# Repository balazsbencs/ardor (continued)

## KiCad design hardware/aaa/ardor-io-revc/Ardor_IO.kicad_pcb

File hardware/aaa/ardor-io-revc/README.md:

# Ardor IO — Rev C, budget SMT

Rev C is an alternate 68 × 46 mm, two-layer board for two-board JLCPCB SMT assembly. It retains DIN MIDI input, passive expression input, mono line output with startup relay mute, and the internal amp feed. Headphones are omitted. The full-featured revision remains in [../ardor-io](../ardor-io/README.md).

Open `Ardor_IO.kicad_pro` in KiCad 9. Use the [connected one-page schematic](review/Ardor_IO_connected.pdf) to follow the circuit, or [Ardor_IO.pdf](Ardor_IO.pdf) for the five editable schematic sheets. The [assembly guide](assembly/README.md) contains the Gerber ZIP, exact JLCPCB BOM, CPL and placement reference.

| For two assembled boards | Previous revision | Rev C |
| --- | ---: | ---: |
| SMT placements per board | 76 | 60 |
| Unique SMT parts | 28 | 24 |
| Extended part types | 15 | 8 |
| Modelled components, including minimums/loss | $39.06 | $16.57 |
| Economic feeder fees at $3.07/type | $46.05 | $24.56 |
| Components + feeder subtotal | $85.11 | $41.13 |

This model predicts **$43.98 less for two boards** in components and feeder fees. It is not a checkout quotation or a guaranteed total. PCB fabrication, setup, stencil, joints, shipping, tax, fixtures, manual parts and discounts are outside the subtotal. The earlier user quote was $108 for two assembled boards; its fee breakdown was not provided. See [cost-comparison.json](assembly/cost-comparison.json), the dated inventory snapshots and [JLCPCB's current price schedule](https://jlcpcb.com/help/article/pcb-assembly-price). Rev C also removes the headphone QFN and its X-ray inspection requirement.

## Changes and tradeoffs

- Two TI TLV9002IDR SOIC-8 dual op-amps replace three OPA2320 devices. The mono buffer feeds two separate coupling capacitors and source resistors. The line and amp outputs share this buffer; simultaneous loads must meet the specified minimum impedances.
- ADS1115, address 0x48, GPIO mapping, pedal polarity selector, H11L1M optocoupler, relay driver and jack protection remain. Firmware can keep the existing MIDI, expression and line-mute interfaces. GPIO17 is unused.
- Mono averaging resistors are 10 kΩ / 1%, shared with other Basic resistors. Worst-case weights are 0.495 and 0.505; opposite-phase inputs can leave a 1% residual, instead of the previous 0.1% resistor target.
- Supply bulk and audio coupling capacitors use Basic Samsung X5R parts. The 50 V, 1206 audio capacitors retain their nominal 10 µF. X5R has a lower temperature limit than X7R and still has voltage-dependent capacitance, microphonics and distortion that require measurement.
- The three 0603 ferrites are Basic Murata BLM18PG121SN1D, 120 Ω at 100 MHz rather than 600 Ω. DC operation is retained; RF attenuation changes. No assembled-enclosure EMC claim is made.
- The outline and mounting coordinates match the compact board. Removed circuitry leaves spare area; enclosure fit, Pi stack height and panel-jack choices still need mechanical confirmation.
- Ground uses the filled front/back copper: 192 redundant GND track segments (324.13 mm) are removed. Three short local links and all 20 ground vias remain. See the [before/after routing view](routing/ground-routing.svg) and [ground audit](verification/ground-routing-audit.json). CHASSIS and signal routing are unchanged. A smaller outline would require moving components and mounting holes; removing tracks alone does not create that mechanical clearance.
- Both 3.3 V rails use uniform 0.20 mm tracks. Their low current makes wider runs unnecessary; the [width audit](verification/3v3-width-audit.json) checks every segment and a conservative track-resistance estimate. All other track widths and all route centerlines retain the reviewed layout.

The board passes all-severity ERC and DRC, with zero unconnected or parity findings and no exclusions. [Connectivity audit](verification/connectivity-audit.json) checks all **219 electrical pad/net assignments** and 199 intended non-NC connections. The one-page drawing separately checks coverage of all 80 components and wire geometry. This is an engineering prototype; audio, hot-plug, startup and enclosure tests have not been performed.

Read [DESIGN_NOTES.md](DESIGN_NOTES.md) before building. SMT is assembled by JLCPCB; headers, optocoupler, relay, panel connectors and shunts are fitted by hand.

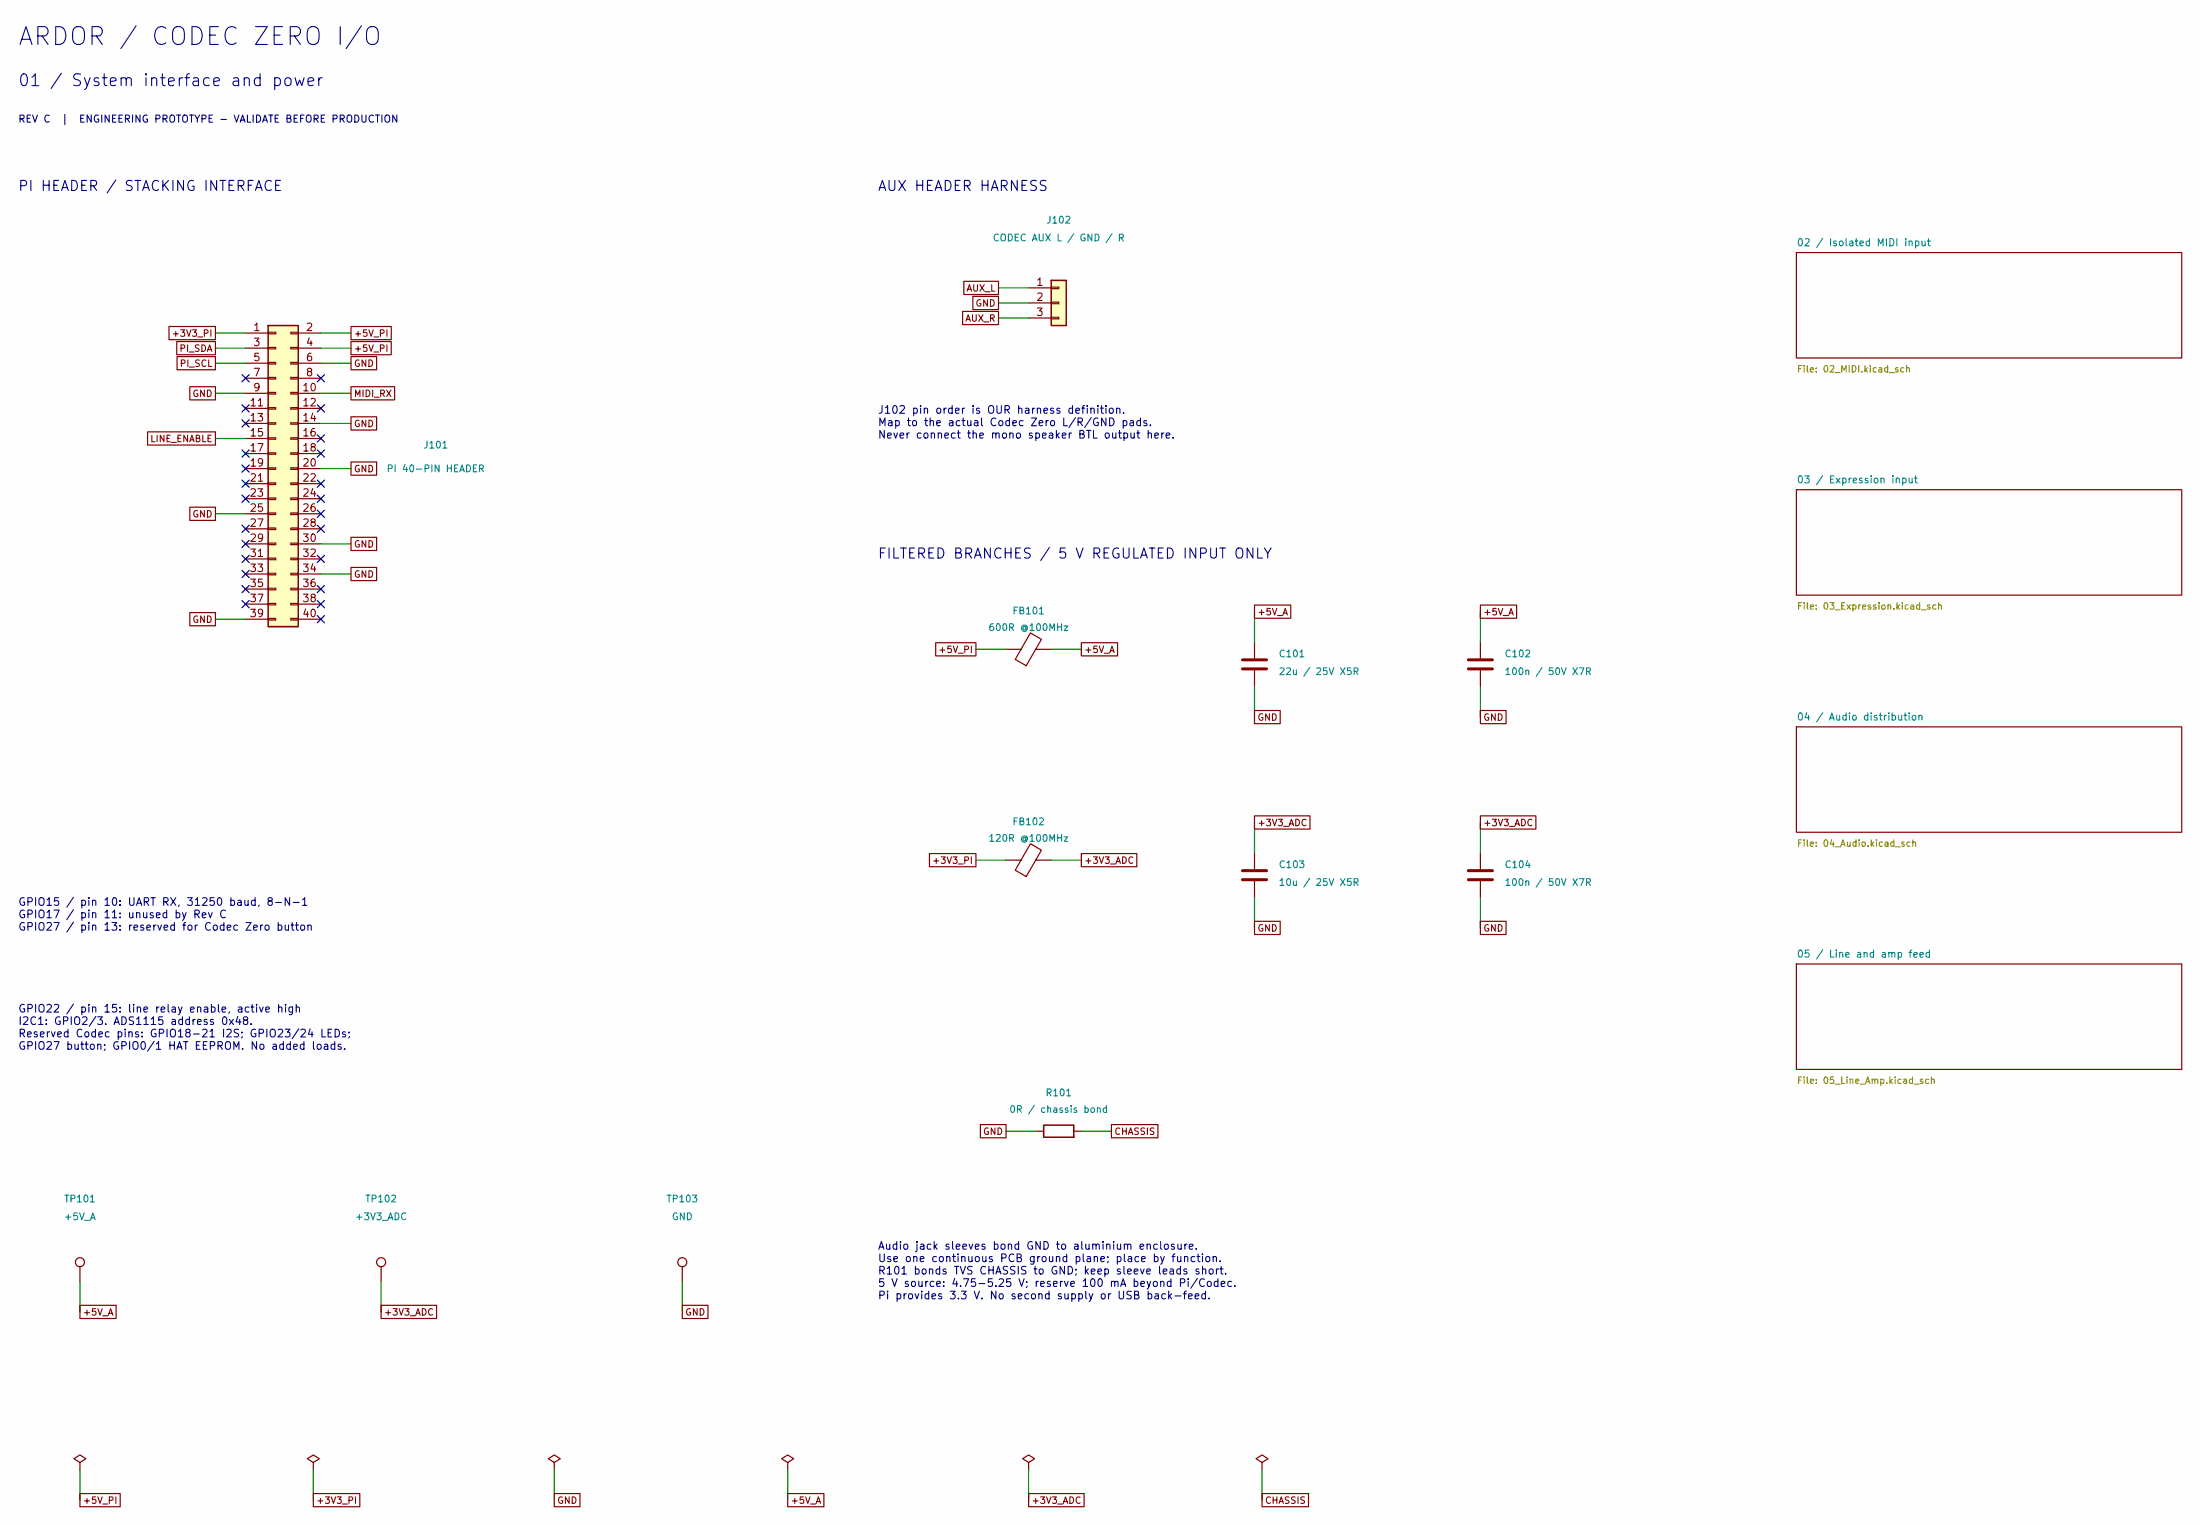
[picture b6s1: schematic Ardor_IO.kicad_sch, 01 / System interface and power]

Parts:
C101: 22u / 25V X5R; C_0805_2012Metric; MPN Samsung Electro-Mechanics CL21A226MAQNN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; JLCPCB Part # C45783
C102, C104: 100n / 50V X7R; C_0603_1608Metric; MPN YAGEO CC0603KRX7R9BB104; JLCPCB Part # C14663
C103: 10u / 25V X5R; C_0805_2012Metric; MPN Samsung Electro-Mechanics CL21A106KAYNN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; JLCPCB Part # C15850
FB101: 600R @100MHz; L_0805_2012Metric; MPN Murata BLM21PG601SN1D; JLCPCB Part # C41556732
FB102: 120R @100MHz; R_0603_1608Metric; MPN Murata Electronics BLM18PG121SN1D; JLCPCB Part # C14709
J101: PI 40-PIN HEADER; PinSocket_2x20_P2.54mm_Vertical; MPN Samtec SSQ-120-03-G-D (verify stack hei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
J102: CODEC AUX L / GND / R; PinHeader_1x03_P2.54mm_Vertical
R101: 0R / chassis bond; R_1206_3216Metric; MPN UNI-ROYAL 1206W4F0000T5E; JLCPCB Part # C17888
TP101: +5V_A; TestPoint_Pad_D1.5mm
TP102: +3V3_ADC; TestPoint_Pad_D1.5mm
TP103: GND; TestPoint_Pad_D1.5mm

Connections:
+3V3_ADC: C103.1, C104.1, FB102.2, TP102.1; also elsewhere on the board
+3V3_PI: FB102.1, J101.1; also elsewhere on the board
+5V_A: C101.1, C102.1, FB101.2, TP101.1; also elsewhere on the board
+5V_PI: FB101.1, J101.2, J101.4; also elsewhere on the board
AUX_L: J102.1; also elsewhere on the board
AUX_R: J102.3; also elsewhere on the board
CHASSIS: R101.2; also elsewhere on the board
GND: C101.2, C102.2, C103.2, C104.2, J101.6, J101.9, J101.14, J101.20, J101.25, J101.30, J101.34, J101.39, J102.2, R101.1, TP103.1; also elsewhere on the board
LINE_ENABLE: J101.15; also elsewhere on the board
MIDI_RX: J101.10; also elsewhere on the board
PI_SCL: J101.5; also elsewhere on the board
PI_SDA: J101.3; also elsewhere on the board

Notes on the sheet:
ARDOR / CODEC ZERO I/O
01 / System interface and power
REV C | ENGINEERING PROTOTYPE - VALIDATE BEFORE PRODUCTION
PI HEADER / STACKING INTERFACE
GPIO15 / pin 10: UART RX, 31250 baud, 8-N-1 GPIO17 / pin 11: unused by Rev C GPIO27 / pin 13: reserved for Codec Zero button
GPIO22 / pin 15: line relay enable, active high I2C1: GPIO2/3. ADS1115 address 0x48. Reserved Codec pins: GPIO18-21 I2S; GPIO23/24 LEDs; GPIO27 button; GPIO0/1 HAT EEPROM. No added loads.
AUX HEADER HARNESS
J102 pin order is OUR harness definition. Map to the actual Codec Zero L/R/GND pads. Never connect the mono speaker BTL output here.
FILTERED BRANCHES / 5 V REGULATED INPUT ONLY
Audio jack sleeves bond GND to aluminium enclosure. Use one continuous PCB ground plane; place by function. R101 bonds TVS CHASSIS to GND; keep sleeve leads short. 5 V source: 4.75-5.25 V; reserve 100 mA beyond Pi/Codec. Pi provides 3.3 V. No second supply or USB back-feed.

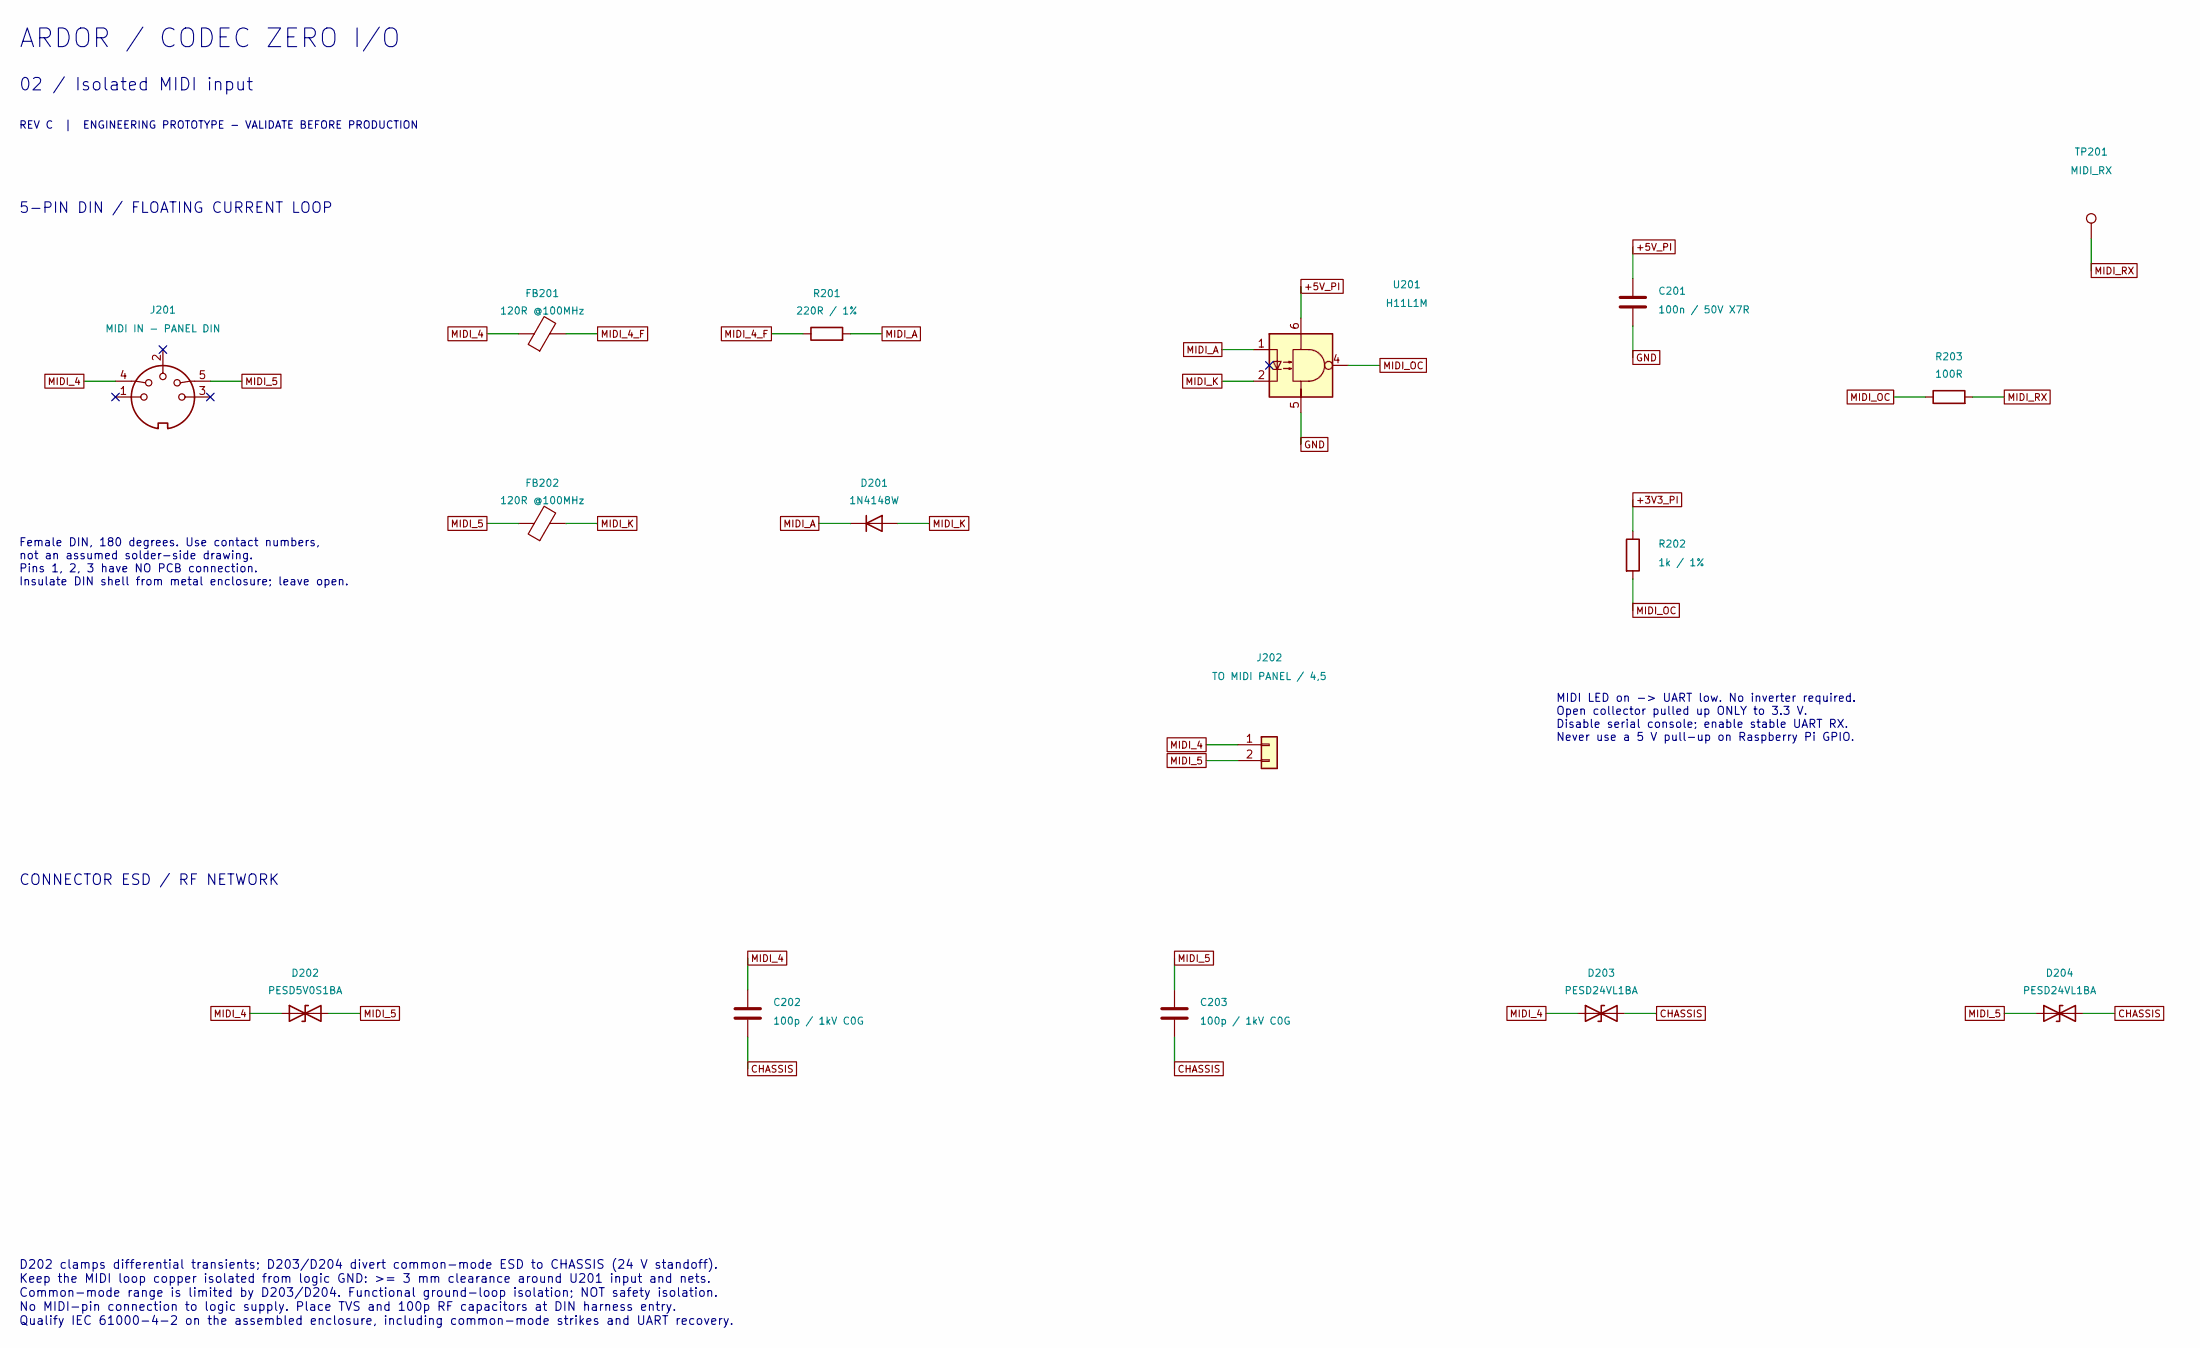
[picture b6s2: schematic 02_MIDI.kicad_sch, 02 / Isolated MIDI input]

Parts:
C201: 100n / 50V X7R; C_0603_1608Metric; MPN YAGEO CC0603KRX7R9BB104; JLCPCB Part # C14663
C202, C203: 100p / 1kV C0G; C_1206_3216Metric; MPN CCTC TCC1206COG101J102DT; JLCPCB Part # C367316
D201: 1N4148W; D_SOD-123; MPN ST(Semtech) 1N4148W; JLCPCB Part # C81598
D202: PESD5V0S1BA; D_SOD-323; MPN Nexperia PESD5V0S1BA,115; JLCPCB Part # C19224
D203, D204: PESD24VL1BA; D_SOD-323; MPN Nexperia PESD24VL1BA,115; JLCPCB Part # C69324
FB201, FB202: 120R @100MHz; R_0603_1608Metric; MPN Murata Electronics BLM18PG121SN1D; JLCPCB Part # C14709
J201: MIDI IN - PANEL DIN
J202: TO MIDI PANEL / 4,5; PinHeader_1x02_P2.54mm_Vertical
R201: 220R / 1%; R_0603_1608Metric; MPN UNI-ROYAL 0603WAF2200T5E; JLCPCB Part # C22962
R202: 1k / 1%; R_0603_1608Metric; MPN UNI-ROYAL 0603WAF1001T5E; JLCPCB Part # C21190
R203: 100R; R_0603_1608Metric; MPN UNI-ROYAL 0603WAF1000T5E; JLCPCB Part # C22775
TP201: MIDI_RX; TestPoint_Pad_D1.5mm
U201: H11L1M; DIP-6_W7.62mm; MPN onsemi H11L1M

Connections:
+3V3_PI: R202.1; also elsewhere on the board
+5V_PI: C201.1, U201.6; also elsewhere on the board
CHASSIS: C202.2, C203.2, D203.2 (A2), D204.2 (A2); also elsewhere on the board
GND: C201.2, U201.5; also elsewhere on the board
MIDI_4: C202.1, D202.1 (A1), D203.1 (A1), FB201.1, J201.4, J202.1
MIDI_4_F: FB201.2, R201.1
MIDI_5: C203.1, D202.2 (A2), D204.1 (A1), FB202.1, J201.5, J202.2
MIDI_A: D201.1 (K), R201.2, U201.1
MIDI_K: D201.2 (A), FB202.2, U201.2
MIDI_OC: R202.2, R203.1, U201.4
MIDI_RX: R203.2, TP201.1; also elsewhere on the board

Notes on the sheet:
ARDOR / CODEC ZERO I/O
02 / Isolated MIDI input
REV C | ENGINEERING PROTOTYPE - VALIDATE BEFORE PRODUCTION
5-PIN DIN / FLOATING CURRENT LOOP
Female DIN, 180 degrees. Use contact numbers, not an assumed solder-side drawing. Pins 1, 2, 3 have NO PCB connection. Insulate DIN shell from metal enclosure; leave open.
MIDI LED on -> UART low. No inverter required. Open collector pulled up ONLY to 3.3 V. Disable serial console; enable stable UART RX. Never use a 5 V pull-up on Raspberry Pi GPIO.
CONNECTOR ESD / RF NETWORK
D202 clamps differential transients; D203/D204 divert common-mode ESD to CHASSIS (24 V standoff). Keep the MIDI loop copper isolated from logic GND: >= 3 mm clearance around U201 input and nets. Common-mode range is limited by D203/D204. Functional ground-loop isolation; NOT safety isolation. No MI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

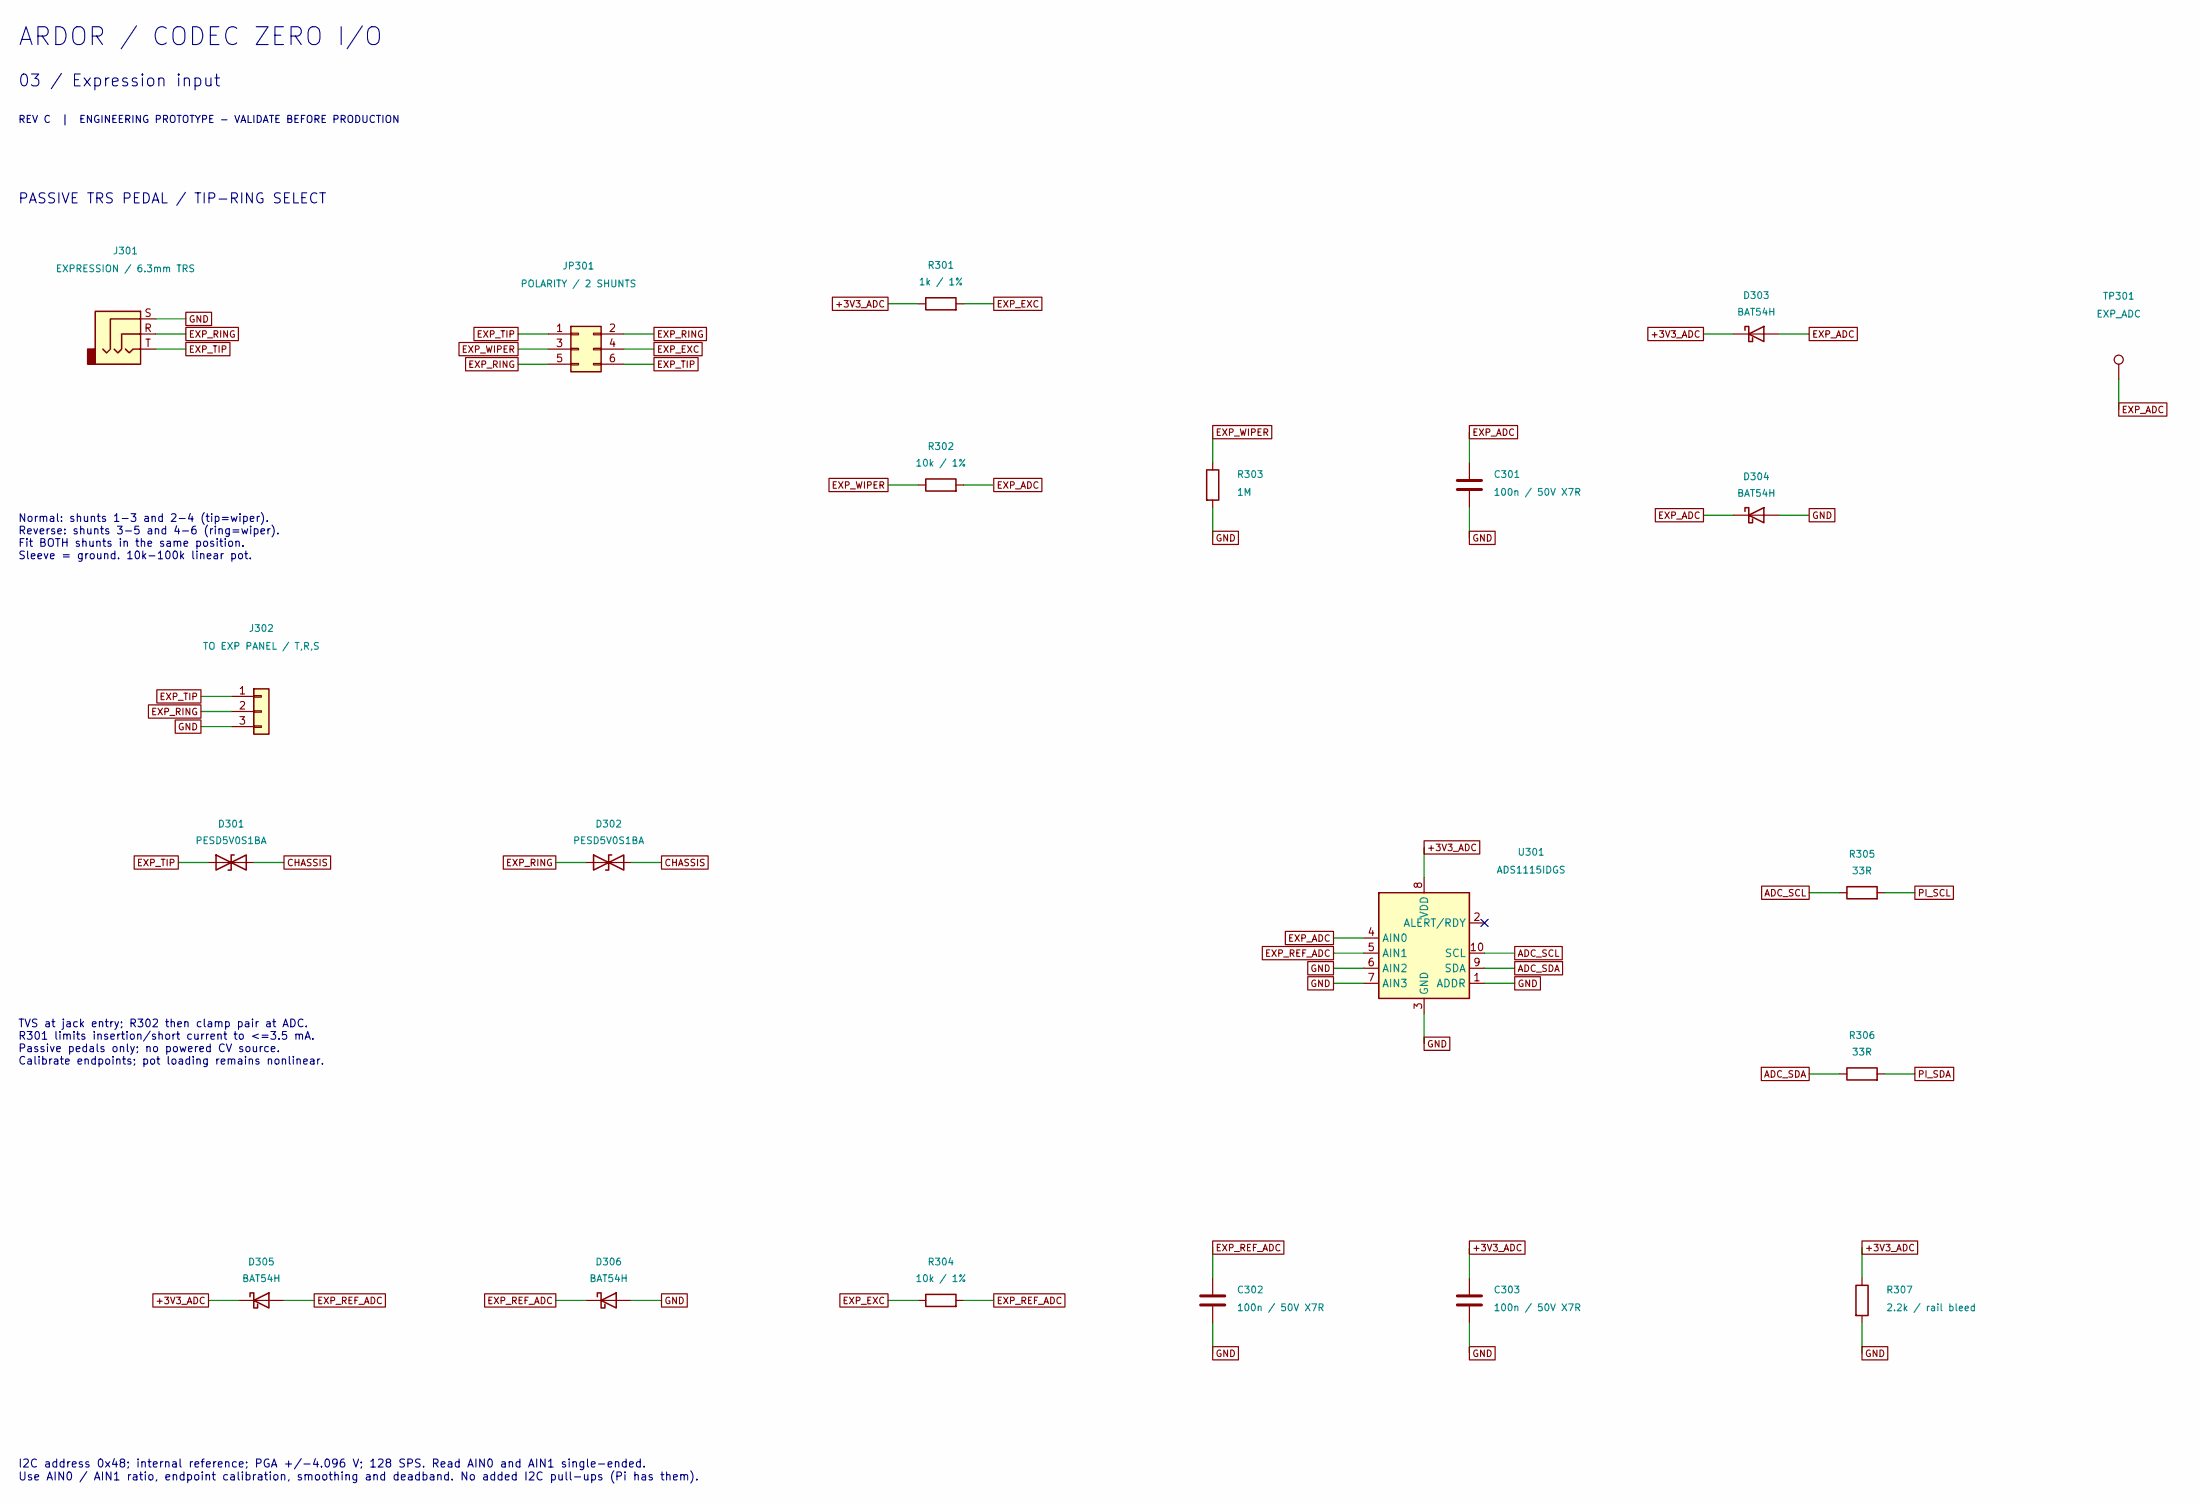
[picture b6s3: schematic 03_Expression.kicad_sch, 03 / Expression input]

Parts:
C301, C302, C303: 100n / 50V X7R; C_0603_1608Metric; MPN YAGEO CC0603KRX7R9BB104; JLCPCB Part # C14663
D301, D302: PESD5V0S1BA; D_SOD-323; MPN Nexperia PESD5V0S1BA,115; JLCPCB Part # C19224
D303, D304, D305, D306: BAT54H; D_SOD-123F; MPN Nexperia BAT54H,115; JLCPCB Part # C426769
J301: EXPRESSION / 6.3mm TRS
J302: TO EXP PANEL / T,R,S; PinHeader_1x03_P2.54mm_Vertical
JP301: POLARITY / 2 SHUNTS; PinHeader_2x03_P2.54mm_Vertical
R301: 1k / 1%; R_0603_1608Metric; MPN UNI-ROYAL 0603WAF1001T5E; JLCPCB Part # C21190
R302, R304: 10k / 1%; R_0603_1608Metric; MPN UNI-ROYAL 0603WAF1002T5E; JLCPCB Part # C25804
R303: 1M; R_0603_1608Metric; MPN UNI-ROYAL 0603WAF1004T5E; JLCPCB Part # C22935
R305, R306: 33R; R_0603_1608Metric; MPN UNI-ROYAL 0603WAF330JT5E; JLCPCB Part # C23140
R307: 2.2k / rail bleed; R_0603_1608Metric; MPN UNI-ROYAL 0603WAF2201T5E; JLCPCB Part # C4190
TP301: EXP_ADC; TestPoint_Pad_D1.5mm
U301: ADS1115IDGS; VSSOP-10_3x3mm_P0.5mm; MPN TI ADS1115IDGSR; JLCPCB Part # C37593

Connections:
+3V3_ADC: C303.1, D303.1 (K), D305.1 (K), R301.1, R307.1, U301.8 (VDD); also elsewhere on the board
ADC_SCL: R305.1, U301.10 (SCL)
ADC_SDA: R306.1, U301.9 (SDA)
CHASSIS: D301.2 (A2), D302.2 (A2); also elsewhere on the board
EXP_ADC: C301.1, D303.2 (A), D304.1 (K), R302.2, TP301.1, U301.4 (AIN0)
EXP_EXC: JP301.4, R301.2, R304.1
EXP_REF_ADC: C302.1, D305.2 (A), D306.1 (K), R304.2, U301.5 (AIN1)
EXP_RING: D302.1 (A1), J301.R, J302.2, JP301.2, JP301.5
EXP_TIP: D301.1 (A1), J301.T, J302.1, JP301.1, JP301.6
EXP_WIPER: JP301.3, R302.1, R303.1
GND: C301.2, C302.2, C303.2, D304.2 (A), D306.2 (A), J301.S, J302.3, R303.2, R307.2, U301.1 (ADDR), U301.3 (GND), U301.6 (AIN2), U301.7 (AIN3); also elsewhere on the board
PI_SCL: R305.2; also elsewhere on the board
PI_SDA: R306.2; also elsewhere on the board

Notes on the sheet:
ARDOR / CODEC ZERO I/O
03 / Expression input
REV C | ENGINEERING PROTOTYPE - VALIDATE BEFORE PRODUCTION
PASSIVE TRS PEDAL / TIP-RING SELECT
Normal: shunts 1-3 and 2-4 (tip=wiper). Reverse: shunts 3-5 and 4-6 (ring=wiper). Fit BOTH shunts in the same position. Sleeve = ground. 10k-100k linear pot.
TVS at jack entry; R302 then clamp pair at ADC. R301 limits insertion/short current to <=3.5 mA. Passive pedals only; no powered CV source. Calibrate endpoints; pot loading remains nonlinear.
I2C address 0x48; internal reference; PGA +/-4.096 V; 128 SPS. Read AIN0 and AIN1 single-ended. Use AIN0 / AIN1 ratio, endpoint calibration, smoothing and deadband. No added I2C pull-ups (Pi has them).

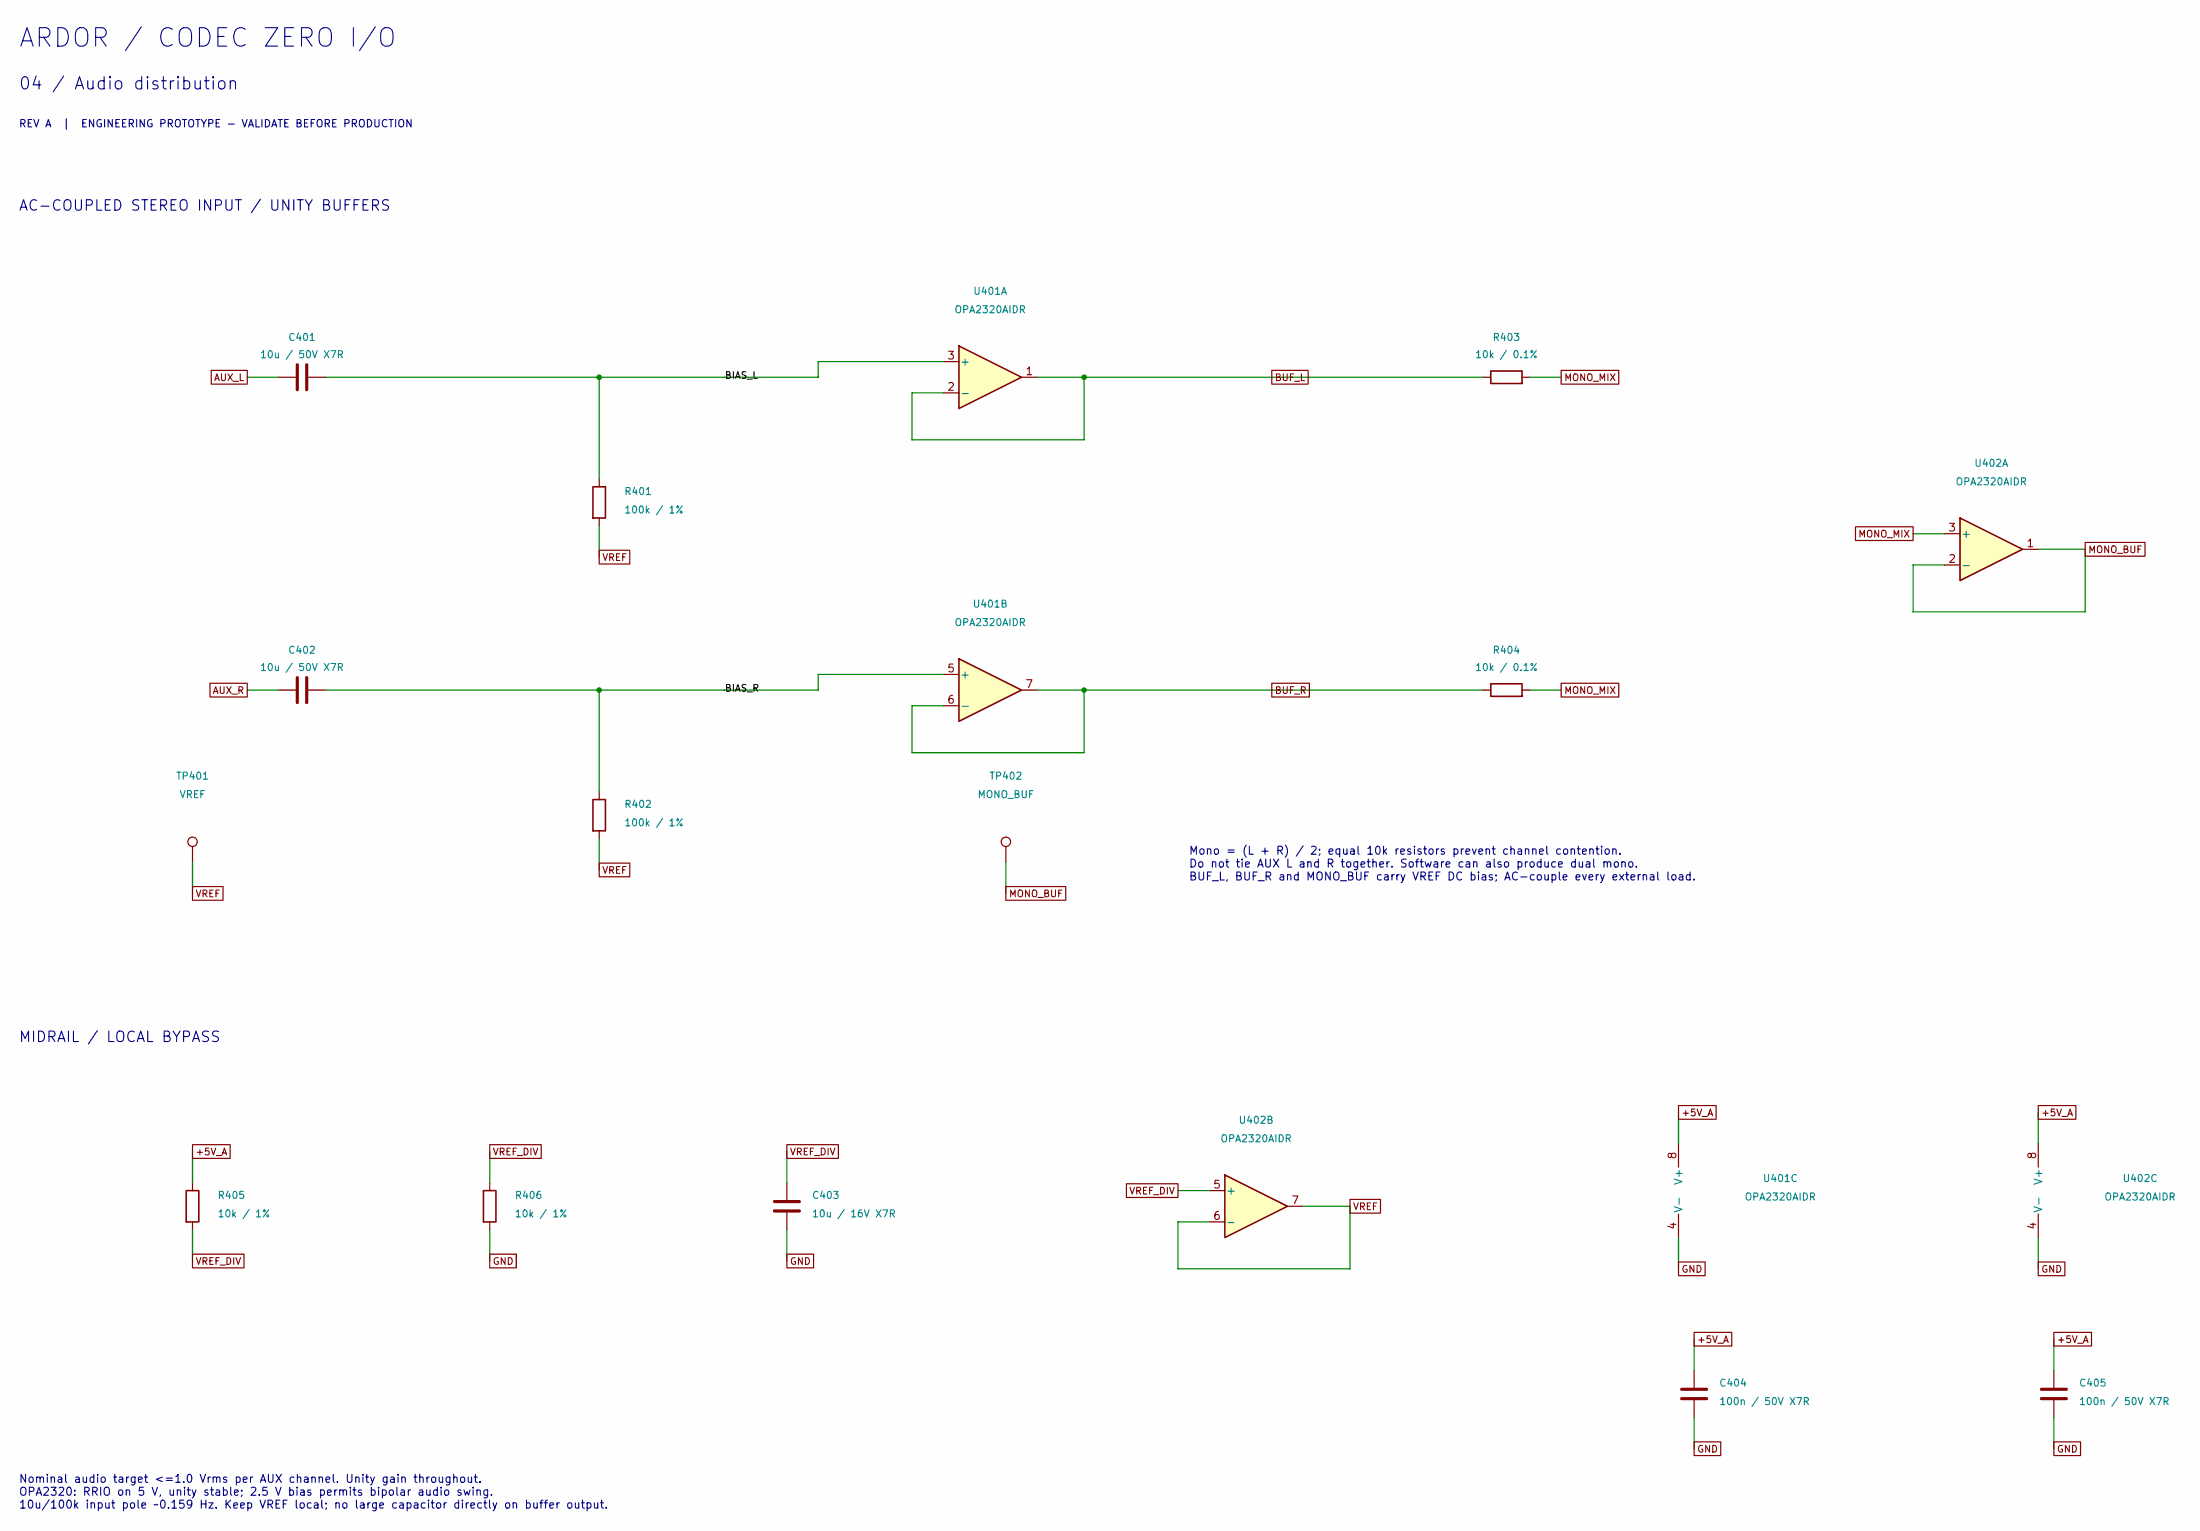
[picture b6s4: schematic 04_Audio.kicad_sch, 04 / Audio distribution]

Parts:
C401, C402: 10u / 50V X7R; C_1206_3216Metric; MPN Samsung CL31B106KBHNNNE; JLCPCB Part # C89632
C403: 10u / 16V X7R; C_0805_2012Metric; MPN Samsung CL21B106KOQNNNE; JLCPCB Part # C95841
C404, C405: 100n / 50V X7R; C_0603_1608Metric; MPN YAGEO CC0603KRX7R9BB104; JLCPCB Part # C14663
R401, R402: 100k / 1%; R_0603_1608Metric; MPN UNI-ROYAL 0603WAF1003T5E; JLCPCB Part # C25803
R403, R404: 10k / 0.1%; R_0603_1608Metric; MPN YAGEO RT0603BRD0710KL; JLCPCB Part # C95204
R405, R406: 10k / 1%; R_0603_1608Metric; MPN UNI-ROYAL 0603WAF1002T5E; JLCPCB Part # C25804
TP401: VREF; TestPoint_Pad_D1.5mm
TP402: MONO_BUF; TestPoint_Pad_D1.5mm
U401, U402: OPA2320AIDR; SOIC-8_3.9x4.9mm_P1.27mm; MPN TI OPA2320AIDR; JLCPCB Part # C2863402

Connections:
+5V_A: C404.1, C405.1, R405.1, U401.8 (V+), U402.8 (V+); also elsewhere on the board
/04 / Audio distribution/BIAS_L: C401.2, R401.1, U401.3 (+)
/04 / Audio distribution/BIAS_R: C402.2, R402.1, U401.5 (+)
/04 / Audio distribution/BUF_L: R403.1, U401.1, U401.2 (-)
/04 / Audio distribution/BUF_R: R404.1, U401.6 (-), U401.7
AUX_L: C401.1; also elsewhere on the board
AUX_R: C402.1; also elsewhere on the board
GND: C403.2, C404.2, C405.2, R406.2, U401.4 (V-), U402.4 (V-); also elsewhere on the board
MONO_MIX: R403.2, R404.2, U402.3 (+)
VREF: R401.2, R402.2, TP401.1, U402.6 (-), U402.7
VREF_DIV: C403.1, R405.2, R406.1, U402.5 (+)

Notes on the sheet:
ARDOR / CODEC ZERO I/O
04 / Audio distribution
REV A | ENGINEERING PROTOTYPE - VALIDATE BEFORE PRODUCTION
AC-COUPLED STEREO INPUT / UNITY BUFFERS
Mono = (L + R) / 2; equal 10k resistors prevent channel contention. Do not tie AUX L and R together. Software can also produce dual mono. BUF_L, BUF_R and MONO_BUF carry VREF DC bias; AC-couple every external load.
MIDRAIL / LOCAL BYPASS
Nominal audio target <=1.0 Vrms per AUX channel. Unity gain throughout. OPA2320: RRIO on 5 V, unity stable; 2.5 V bias permits bipolar audio swing. 10u/100k input pole ~0.159 Hz. Keep VREF local; no large capacitor directly on buffer output.
